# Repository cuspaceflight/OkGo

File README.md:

OkGo
====

*OkGo* is [Cambridge University Space Flight](http://cusf.co.uk)'s
rocket firing controller.

*OkGo* was designed for testing the *Quasar* hybrid rocket motor.  It allowed
remote (over 100m of wire) control of the nitrous oxide valve and firing of the
ignition e-match.  It was constructed using an ad-hoc point-to-point layout.
An entirely passive design, it simply uses mechanical switches to trigger
relays.  It was later upgraded to control two valves, one of which passed a low
flow of nitrous oxide to help start the motor.

*OkGo 2* was a full redesign for the launch of *Martlet 2*.  Due to the
increased safety radius (on the order of 500m) radio control is to be used.  It
will have 4 general purpose (valve or e-match) channels with independent
continuity checking and firing, and separate firing boxes containing current
limiting resistors.

*OkGo 3* is another full redesign for the launch of *Martlet 3*.  It will
continuity check and ignite a single channel with a constant-current drive.
Ignition and control will be small and light for portability.

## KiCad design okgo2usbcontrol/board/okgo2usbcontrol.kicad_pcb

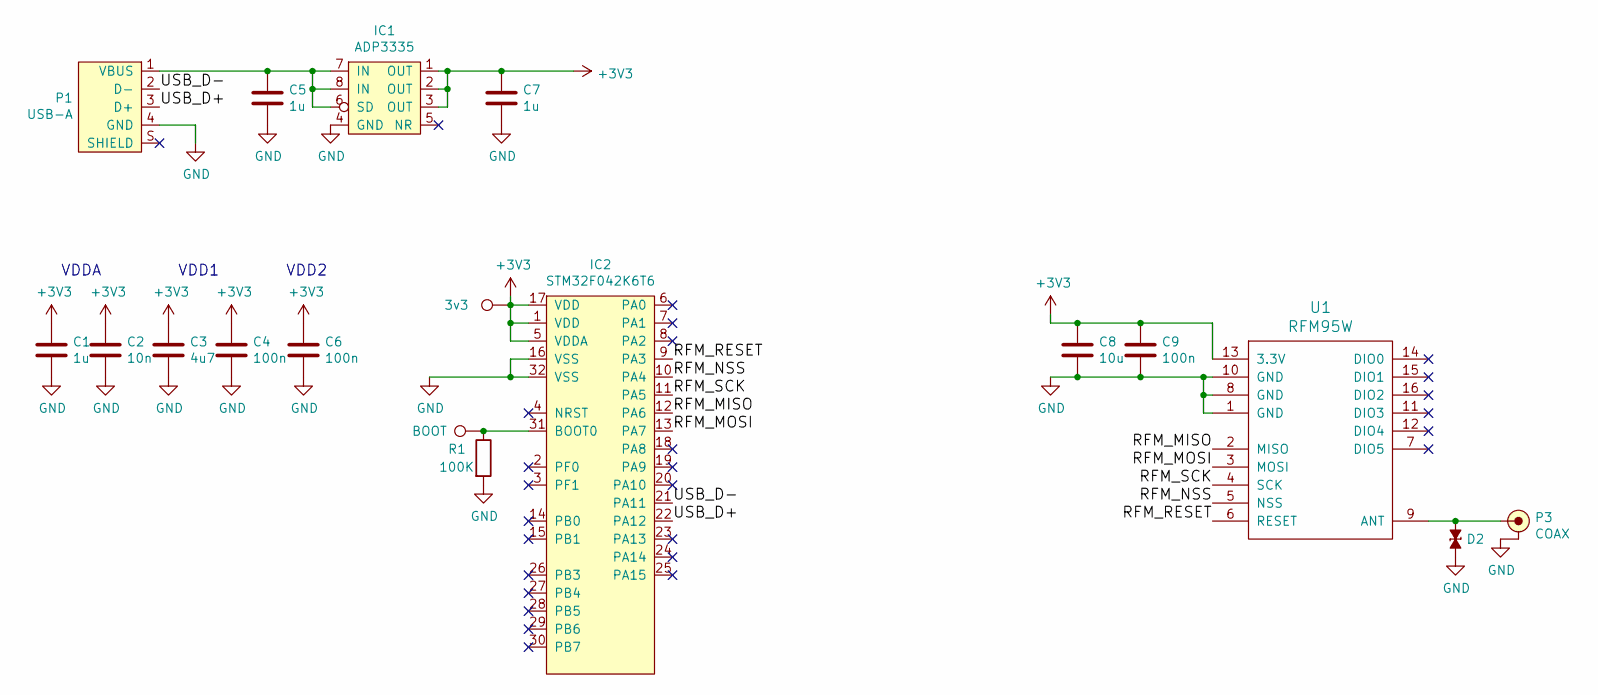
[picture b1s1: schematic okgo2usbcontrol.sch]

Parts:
C1, C5, C7: 1u; 0402
C2: 10n; 0402
C3: 4u7; 0402
C4, C6, C9: 100n; 0402
C8: 10u; 0402
D2: ESD_DIODE; 0603
IC1: ADP3335; MSOP-8; Farnell 2067775
IC2: STM32F042K6T6; LQFP-32; Farnell 2750629
P1: USB-A; USB-A_M_Edge; Farnell 2067044
P3: COAX; SMA-EDGE; Farnell 1608592
R1: 100K; 0402
U1: RFM95W
W1: BOOT; PokyPad
W2: 3v3; PokyPad

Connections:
+3V3: C1.1, C2.1, C3.1, C4.1, C6.1, C7.1, C8.1, C9.1, IC1.1 (OUT), IC1.2 (OUT), IC1.3 (OUT), IC2.1 (VDD), IC2.5 (VDDA), IC2.17 (VDD), U1.13 (3.3V), W2.1
/RFM_MISO: IC2.12 (PA6), U1.2 (MISO)
/RFM_MOSI: IC2.13 (PA7), U1.3 (MOSI)
/RFM_NSS: IC2.10 (PA4), U1.5 (NSS)
/RFM_RESET: IC2.9 (PA3), U1.6 (RESET)
/RFM_SCK: IC2.11 (PA5), U1.4 (SCK)
/USB_D+: IC2.22 (PA12), P1.3 (D+)
/USB_D-: IC2.21 (PA11), P1.2 (D-)
GND: C1.2, C2.2, C3.2, C4.2, C5.2, C6.2, C7.2, C8.2, C9.2, D2.2, IC1.4 (GND), IC2.16 (VSS), IC2.32 (VSS), P1.4 (GND), P3.2 (GND), R1.2, U1.1 (GND), U1.8 (GND), U1.10 (GND)
unnamed: C5.1, IC1.6 (SD), IC1.7 (IN), IC1.8 (IN), P1.1 (VBUS)
unnamed: D2.1, P3.1 (RF), U1.9 (ANT)
unnamed: IC2.31 (BOOT0), R1.1, W1.1

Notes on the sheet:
VDDA
VDD1
VDD2

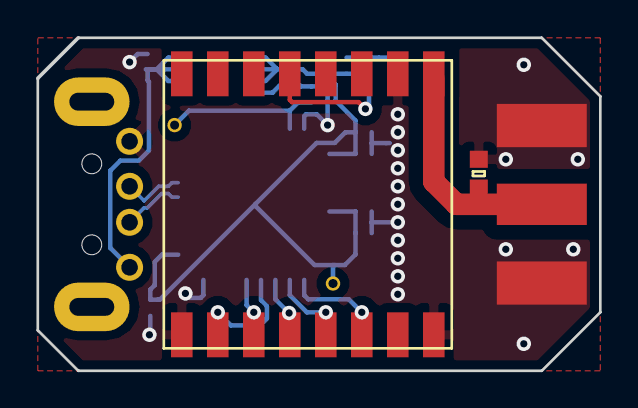
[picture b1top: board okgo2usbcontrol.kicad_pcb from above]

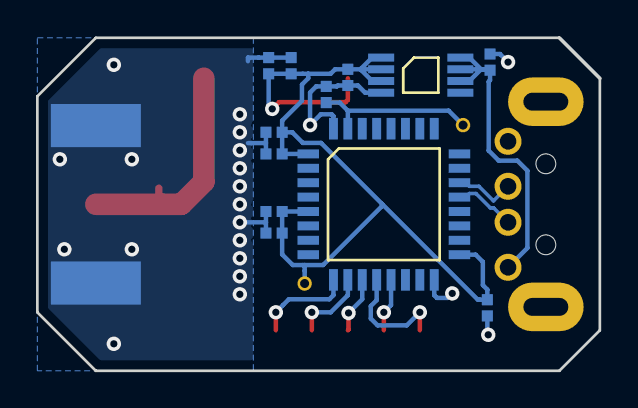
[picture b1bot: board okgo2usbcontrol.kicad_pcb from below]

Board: 2 copper layers, 31.2 x 18.5 mm, 18 parts (14 on the bottom side), 12 nets.

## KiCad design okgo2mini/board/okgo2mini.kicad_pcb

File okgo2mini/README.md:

# Design
* A mini version of OkGo 2 ignition, compatible with OkGo 2 control
* Use STM32F0 and RFM95W circuit from OkGo 2 ignition
    * If I'm careful I could make it pin-compatible and use the same firmware
      as OkGo 2, or just with minimal modification
* Use battery charge/management circuit from Toad/Linetime
    * Has only had minimal testing on Linetime. Wait for Toad to be tested
      before committing to this.
* Use 1A constant current firer from latest m3pyro
# Parts
* Nana plugs: red CN16308 black CN16305
* High retention red USB-B 1753809
* Red Hammond extruded aluminium case 2469292

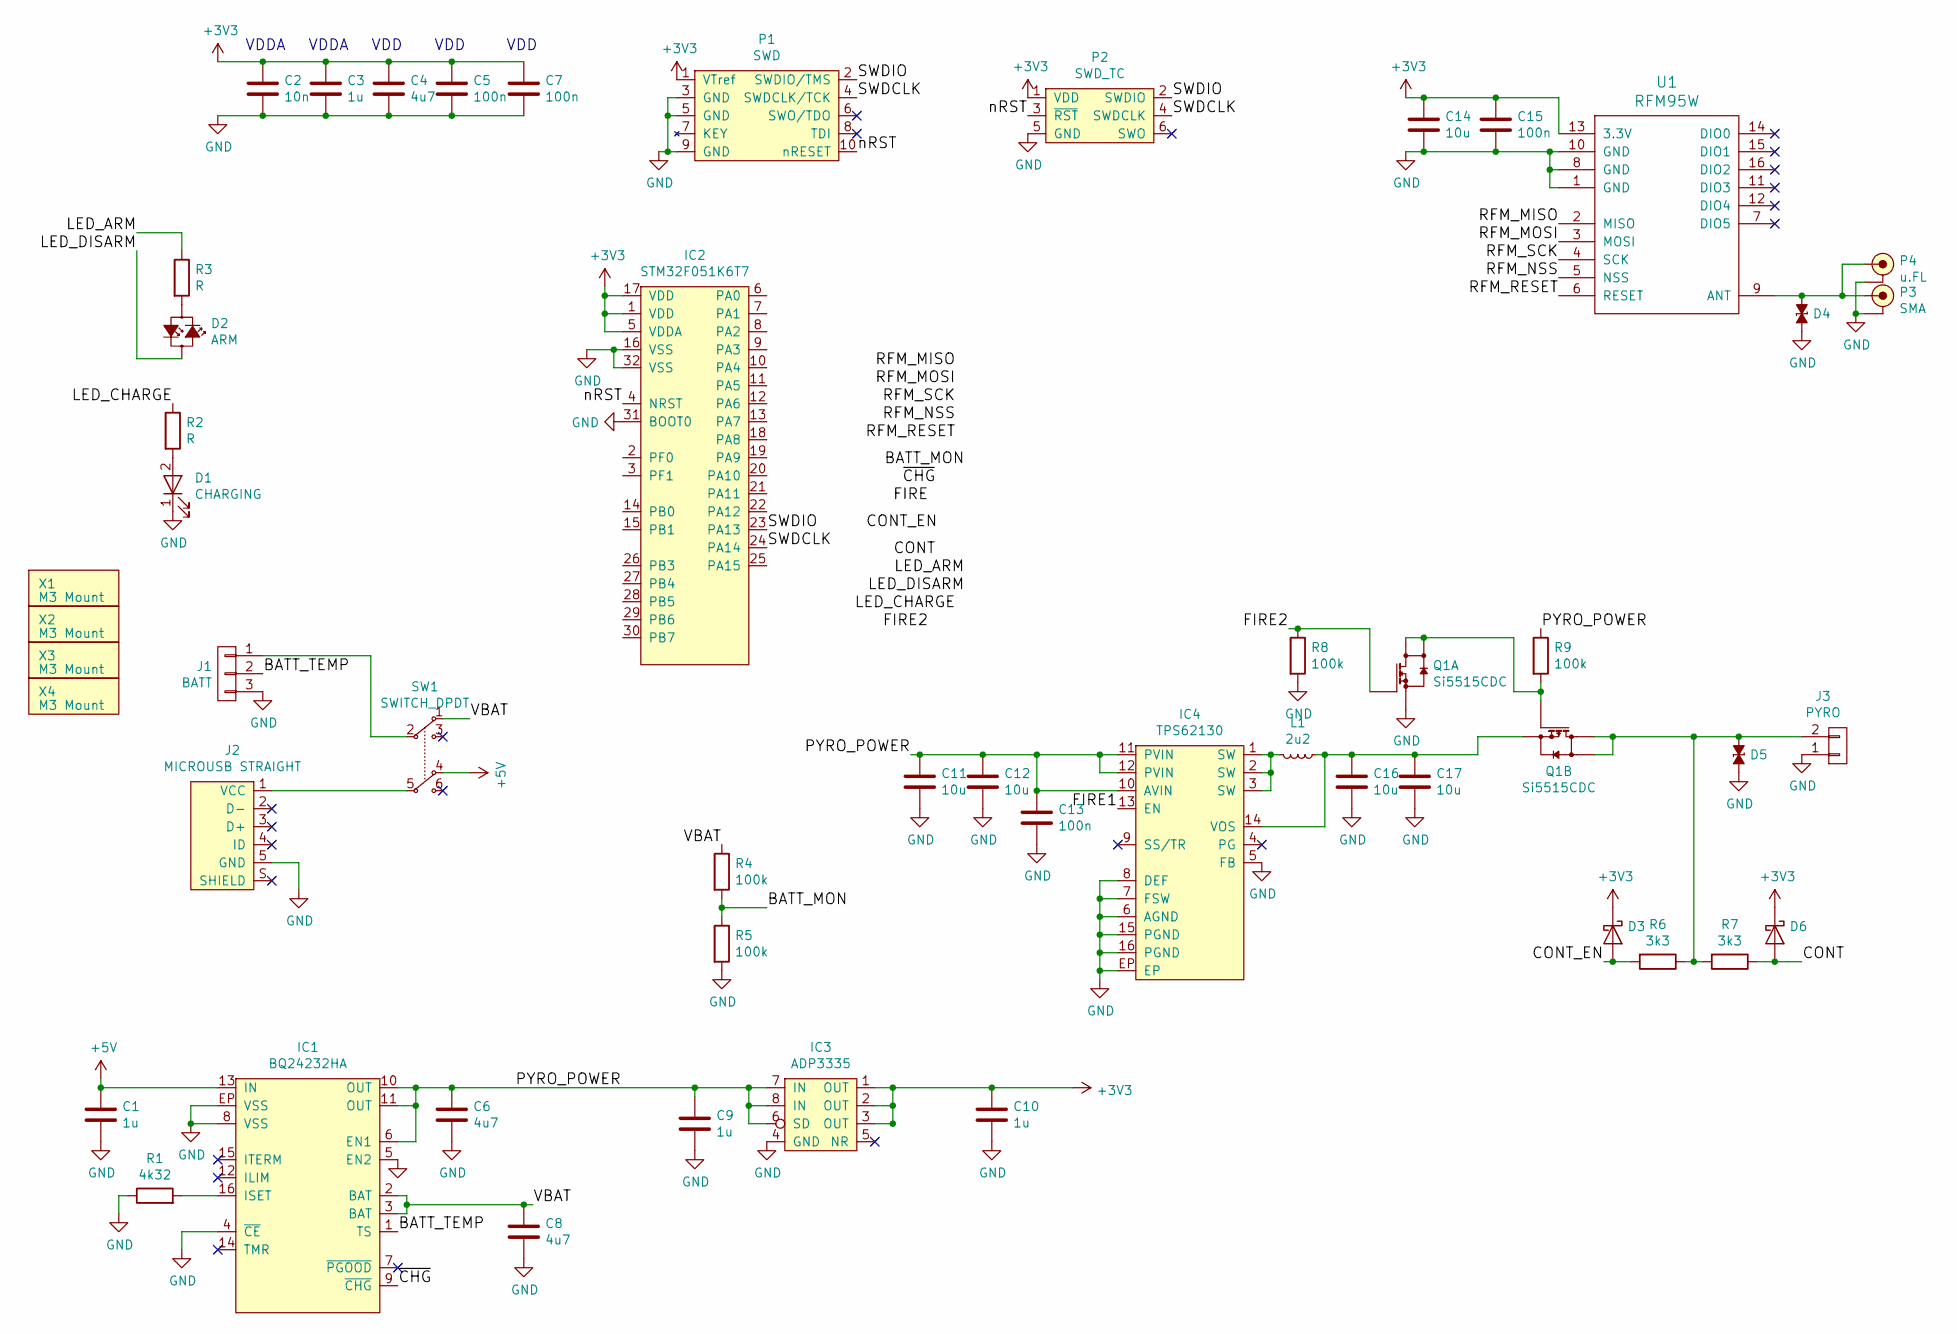
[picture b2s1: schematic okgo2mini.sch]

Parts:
C1, C3, C9, C10: 1u; 0603
C2: 10n; 0603
C4, C6, C8: 4u7; 0603
C5, C7, C13, C15: 100n; 0603
C11, C12, C14, C16, C17: 10u; 0603
D1: CHARGING; LED_D3.0mm; Farnell 2610420
D2: ARM; LED_D3.0mm; Farnell 2079908
D3, D6: PMEG2005AEA; SOD-323; Farnell 8737843
D4, D5: ESD_DIODE; 0603; Farnell 2368173
IC1: BQ24232HA; QFN-16-EP-TI; Farnell 2576286
IC2: STM32F051K6T7; LQFP-32; Farnell 2432085
IC3: ADP3335; MSOP-8; Farnell 2067775
IC4: TPS62130; QFN-16-EP-TI; Farnell 2361246
J1: BATT; S03B-PASK-2
J2: MICROUSB STRAIGHT; USB_Micro_B_Vertical; Farnell 2614949
J3: PYRO; S02B-PASK-2
L1: 2u2; XFL4020; Farnell 2289216
P1: SWD; FTSH-105-01-F-D-K
P2: SWD_TC; TC2030-NL
P3: SMA; SMA-EDGE; Farnell 1608592
P4: u.FL; uFL-R-SMT; Farnell 1688077
Q1: Si5515CDC; ChipFET-1206-8; Farnell 2335332
R1: 4k32; 0603
R2, R3: R; 0603
R4, R5, R8, R9: 100k; 0603
R6, R7: 3k3; 0603
SW1: SWITCH_DPDT; 120x-M1-xx-C; Farnell 9574743
U1: RFM95W; Farnell RF00490
X1, X2, X3, X4: M3 Mount; M3_MOUNT

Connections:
+3V3: C2.1, C3.1, C4.1, C5.1, C7.1, C10.1, C14.1, C15.1, D3.1 (K), D6.1 (K), IC2.1 (VDD), IC2.5 (VDDA), IC2.17 (VDD), IC3.1 (OUT), IC3.2 (OUT), IC3.3 (OUT), P1.1 (VTref), P2.1 (VDD), U1.13 (3.3V)
+5V: C1.1, IC1.13 (IN), SW1.4
/BATT_MON: R4.2, R5.1
/BATT_TEMP: IC1.1 (TS), J1.2
/CONT: D6.2 (A), R7.1
/CONT_EN: D3.2 (A), R6.2
/FIRE1: IC4.13 (EN)
/FIRE2: Q1.2 (G1), R8.1
/LED_ARM: R3.1
/LED_CHARGE: R2.1
/LED_DISARM: D2.2 (A)
/PYRO_POWER: C6.1, C9.1, C11.1, C12.1, C13.1, IC1.6 (EN1), IC1.10 (OUT), IC1.11 (OUT), IC3.6 (SD), IC3.7 (IN), IC3.8 (IN), IC4.10 (AVIN), IC4.11 (PVIN), IC4.12 (PVIN), R9.1
/RFM_MISO: U1.2 (MISO)
/RFM_MOSI: U1.3 (MOSI)
/RFM_NSS: U1.5 (NSS)
/RFM_RESET: U1.6 (RESET)
/RFM_SCK: U1.4 (SCK)
/SWDCLK: IC2.24 (PA14), P1.4 (SWDCLK/TCK), P2.4 (SWDCLK)
/SWDIO: IC2.23 (PA13), P1.2 (SWDIO/TMS), P2.2 (SWDIO)
/VBAT: C8.1, IC1.2 (BAT), IC1.3 (BAT), R4.1, SW1.1
/nRST: IC2.4 (NRST), P1.10 (nRESET), P2.3 (~RST)
/~CHG: IC1.9 (~CHG)
GND: C1.2, C2.2, C3.2, C4.2, C5.2, C6.2, C7.2, C8.2, C9.2, C10.2, C11.2, C12.2, C13.2, C14.2, C15.2, C16.2, C17.2, D1.1 (K), D4.2, D5.2, IC1.4 (~CE), IC1.5 (EN2), IC1.8 (VSS), IC1.EP (VSS), IC2.16 (VSS), IC2.31 (BOOT0), IC2.32 (VSS), IC3.4 (GND), IC4.5 (FB), IC4.6 (AGND), IC4.7 (FSW), IC4.8 (DEF), IC4.15 (PGND), IC4.16 (PGND), IC4.EP, J1.3, J2.5 (GND), J3.1, P1.3 (GND), P1.5 (GND), P1.9 (GND), P2.5 (GND), P3.2 (GND), P4.2 (GND), Q1.1 (S1), R1.1, R5.2, R8.2, U1.1 (GND), U1.8 (GND), U1.10 (GND)
unnamed: C16.1, C17.1, IC4.14 (VOS), L1.1, Q1.3 (S2)
unnamed: D1.2 (A), R2.2
unnamed: D2.1 (K), R3.2
unnamed: D4.1, P3.1 (RF), P4.1 (RF), U1.9 (ANT)
unnamed: D5.1, J3.2, Q1.5 (D2), Q1.6 (D2), R6.1, R7.2
unnamed: IC1.16 (ISET), R1.2
unnamed: IC4.1 (SW), IC4.2 (SW), IC4.3 (SW), L1.2
unnamed: J1.1, SW1.2
unnamed: J2.1 (VCC), SW1.5
unnamed: Q1.4 (G2), Q1.7 (D1), Q1.8 (D1), R9.2

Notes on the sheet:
VDDA
VDD

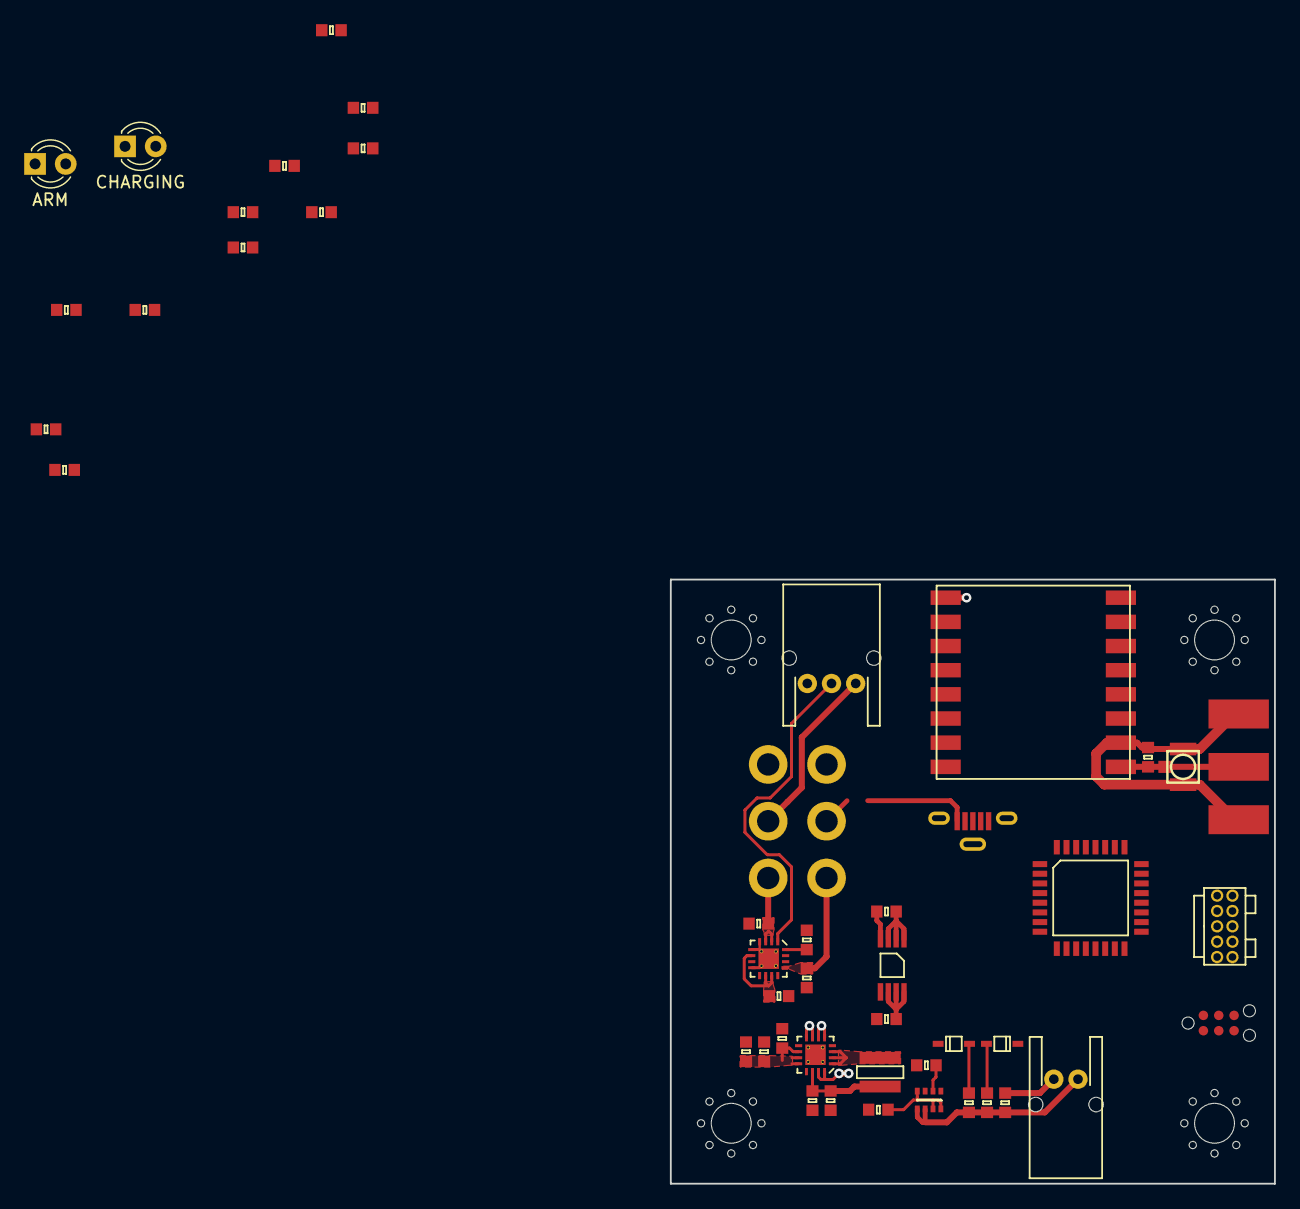
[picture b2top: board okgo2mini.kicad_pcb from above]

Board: 2 copper layers, 50.0 x 50.0 mm, 51 parts (1 on the bottom side), 23 nets.

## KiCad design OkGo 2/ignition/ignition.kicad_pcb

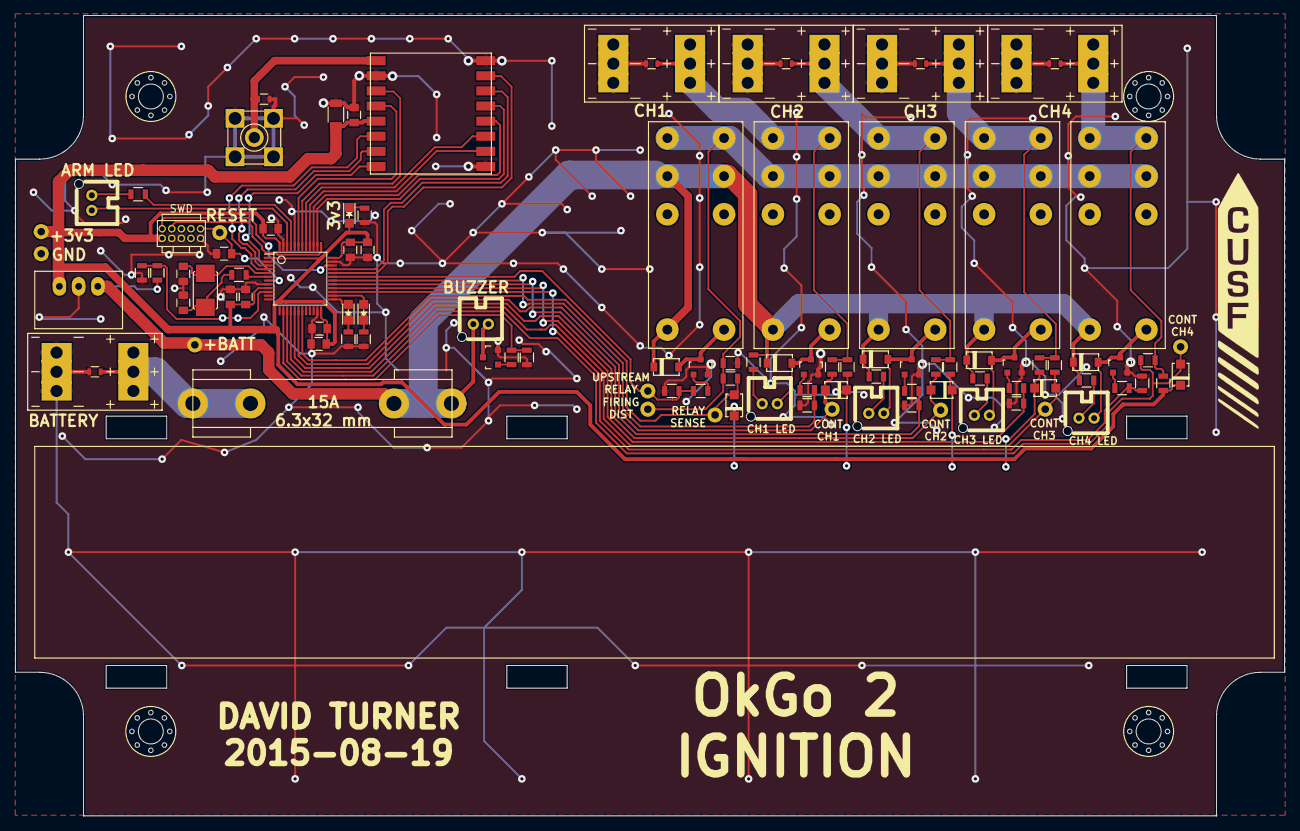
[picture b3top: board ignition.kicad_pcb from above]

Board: 2 copper layers, 167.9 x 105.9 mm, 108 parts (0 on the bottom side), 63 nets.

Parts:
C101, C102, C104, C105, C109: 100n; C_0805
C103, C106: 4u7; C_0805
C107: 10n; C_0805
C108: 100u; C_1206
C110: 1u; C_0805
C111, C112: 15p; C_0805
D101, D103, D206, D210, D214, D218: TVS_small; R_0603
D104: RED; LED-0805
D105: GREEN; LED-0805
D106: YELLOW; LED-0805
D201, D205, D209, D213, D217: MBR2H200SFT1G; SOD-123FL
D202, D204, D208, D212, D216: D; SOD-123F
F101: 6.3x32; 6x32_fuseclip
K201, K202, K203, K204, K205: 16A SPST; Relay_RT314
M3_MOUNT, M3_MOUNT#2, M3_MOUNT#3, M3_MOUNT#4: VAL**; M3_MOUNT_FANCY
P105: BATT; PCB_SPADE
P107: ARM_LED; JST-PA-2-VERT
P109: BUZZ; JST-PA-2-VERT
P111: SMA; SMA_upright
P201: CH3_LED; JST-PA-2-VERT
P203: CH3; PCB_SPADE
P204: CH1_LED; JST-PA-2-VERT
P206: CH1; PCB_SPADE
P207: CH4_LED; JST-PA-2-VERT
P209: CH4; PCB_SPADE
P210: CH2_LED; JST-PA-2-VERT
P212: CH2; PCB_SPADE
Q101, Q201, Q202, Q203, Q204, Q205: BSS138BK; SOT-23
R101, R207, R212, R217, R222: 10k; R_0805
R102: 3k3; R_0805
R103: 75R; R_0805
R104: 100R; R_0805
R105, R201, R208, R213, R218, R223: 180R; R_0805
R106, R202, R204, R210, R214, R220, R224: 100k; R_0805
R107, R108, R109: R; R_0805
R203, R206, R211, R216, R221: 1k; R_0805
R205, R215: 430; R_0805
R209: 510R; R_0805
R219: 510; R_0805
TP101: BATT; TESTPOINT
TP102: GND; TESTPOINT
TP103: nRST; TESTPOINT
TP104: 3v3; TESTPOINT
TP201: FiringDist; TESTPOINT
TP202: USRelay; TESTPOINT
TP203: RelaySense; TESTPOINT
TP204: ContCH3; TESTPOINT
TP205: ContCH1; TESTPOINT
TP206: ContCH4; TESTPOINT
TP207: ContCH2; TESTPOINT
U103: SWD; FTSH-105-01-F-D-K
U105: RFM95W
U106: STM32F071CBT6; LQFP48_ST
U107: TSR 0.5-2433; TSR-0_5
Y101: 8MHz; XTAL50x32

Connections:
+3V3: C101.1, C102.1, C103.1, C105.1, C106.1, C107.1, C108.1, C109.1, C110.1, D104.2, D202.1, D204.1, D208.1, D212.1, D216.1, R206.1, R211.1, R216.1, R221.1, TP104.1, U103.1, U105.13, U106.1, U106.9, U106.24, U106.36, U106.48, U107.3
+BATT: D201.1, D205.1, D209.1, D213.1, D217.1, F101.2, K201.2, K201.3, K202.2, K203.2, K204.2, K205.2, P109.2, R101.1, R205.2, R209.2, R215.2, R219.2, TP101.1, U107.1
/ARM_LED: R103.2, U106.45
/BATT_MON: R101.2, R102.1, U106.10
/BUZZER: R105.2, R106.1, U106.14
/DISARM_LED: P107.1, U106.46
/RFM_DIO0: U105.14, U106.4
/RFM_DIO1: U105.15, U106.3
/RFM_DIO2: U105.16, U106.2
/RFM_DIO3: U105.11, U106.42
/RFM_DIO4: U105.12, U106.43
/RFM_DIO5: U105.7, U106.32
/RFM_MISO: U105.2, U106.40
/RFM_MOSI: U105.3, U106.41
/RFM_NSS: U105.5, U106.38
/RFM_RESET: U105.6, U106.33
/RFM_SCK: U105.4, U106.39
/SWDCLK: U103.4, U106.37
/SWDIO: U103.2, U106.34
/firing/CONT_CH1: D208.2, R212.1, TP205.1, U106.18
/firing/CONT_CH2: D216.2, R222.1, TP207.1, U106.17
/firing/CONT_CH3: D204.2, R207.1, TP204.1, U106.16
/firing/CONT_CH4: D212.2, R217.1, TP206.1, U106.15
/firing/FIRE_CH1: R213.2, R214.1, U106.30
/firing/FIRE_CH2: R223.2, R224.1, U106.29
/firing/FIRE_CH3: R208.2, R210.1, U106.28
/firing/FIRE_CH4: R218.2, R220.1, U106.27
/firing/FIRING_DIST: K201.4, K202.3, K203.3, K204.3, K205.3, R203.2, R204.1, TP201.1
/firing/RELAY_SENSE: D202.2, R203.1, TP203.1, U106.19
/firing/UPSTREAM_RELAY: R201.2, R202.2, TP202.1, U106.31
/nRST: C104.1, TP103.1, U103.10, U106.7
GND: C101.2, C102.2, C103.2, C104.2, C105.2, C106.2, C107.2, C108.2, C109.2, C110.2, C111.2, C112.2, D101.2, D103.2, D206.2, D210.2, D214.2, D218.2, P105.1, P111.2, P111.3, P111.4, P111.5, P203.1, P206.1, P209.1, P212.1, Q101.2, Q201.2, Q202.2, Q203.2, Q204.2, Q205.2, R102.2, R106.2, R107.2, R108.2, R109.2, R202.1, R204.2, R210.2, R214.2, R220.2, R224.2, TP102.1, U103.3, U103.5, U103.9, U105.1, U105.8, U105.10, U106.8, U106.23, U106.35, U106.44, U106.47, U107.2
unnamed: C111.1, R104.1, Y101.2
unnamed: C112.1, U106.5, Y101.1
unnamed: D101.1, F101.1, P105.2
unnamed: D103.1, P111.1, U105.9
unnamed: D104.1, R107.1
unnamed: D105.1, R108.1
unnamed: D105.2, U106.25
unnamed: D106.1, R109.1
unnamed: D106.2, U106.26
unnamed: D201.2, K201.1, Q201.3
unnamed: D205.2, K202.1, P201.1, Q202.3
unnamed: D206.1, K202.4, P203.2, R206.2, R207.2
unnamed: D209.2, K203.1, P204.1, Q203.3
unnamed: D210.1, K203.4, P206.2, R211.2, R212.2
unnamed: D213.2, K204.1, P207.1, Q204.3
unnamed: D214.1, K204.4, P209.2, R216.2, R217.2
unnamed: D217.2, K205.1, P210.1, Q205.3
unnamed: D218.1, K205.4, P212.2, R221.2, R222.2
unnamed: P107.2, R103.1
unnamed: P109.1, Q101.3
unnamed: P201.2, R205.1
unnamed: P204.2, R209.1
unnamed: P207.2, R215.1
unnamed: P210.2, R219.1
unnamed: Q101.1, R105.1
unnamed: Q201.1, R201.1
unnamed: Q202.1, R208.1
unnamed: Q203.1, R213.1
unnamed: Q204.1, R218.1
unnamed: Q205.1, R223.1
unnamed: R104.2, U106.6

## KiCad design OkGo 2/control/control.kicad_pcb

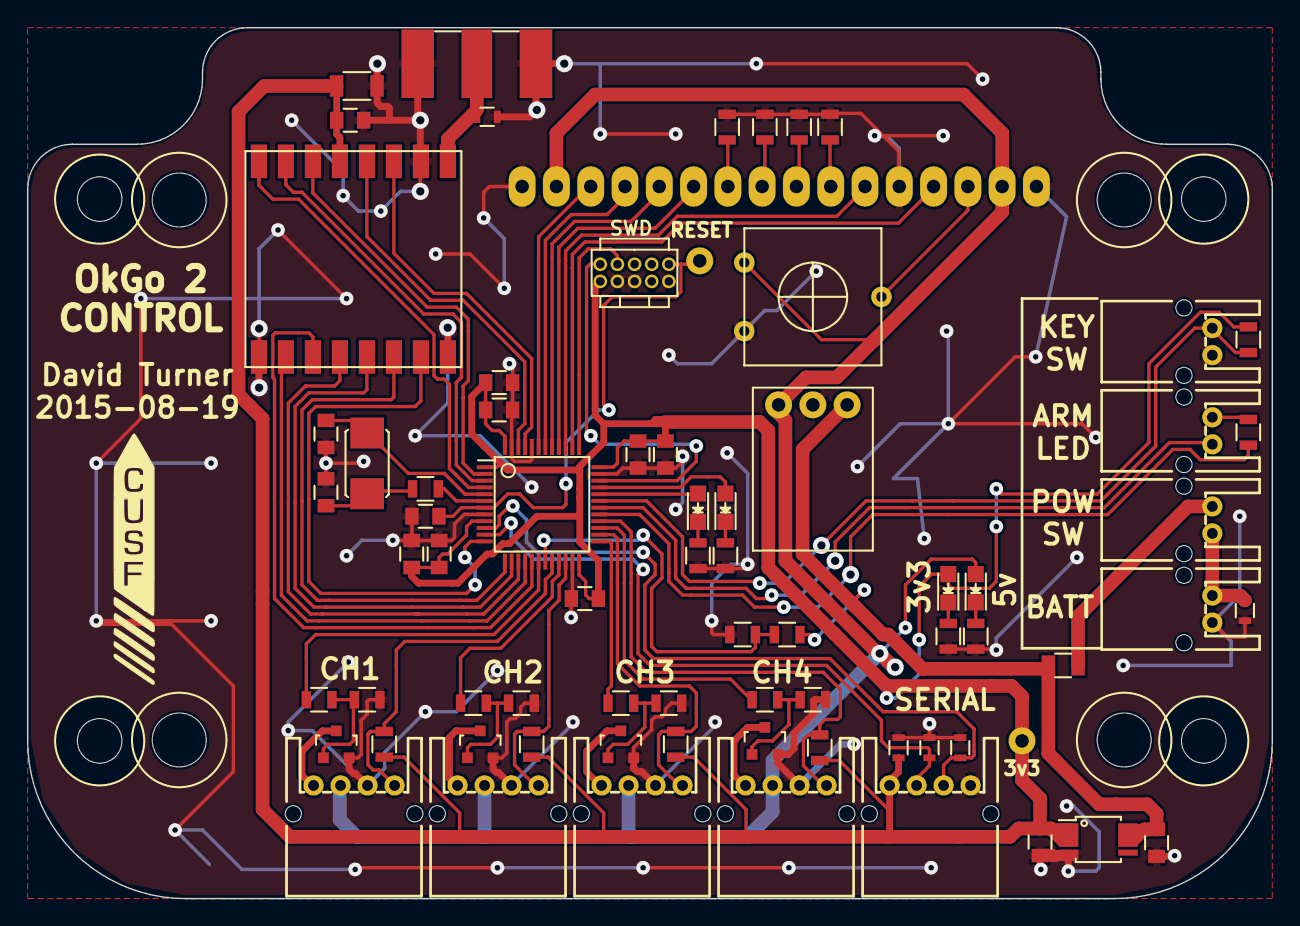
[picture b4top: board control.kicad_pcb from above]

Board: 2 copper layers, 92.2 x 64.5 mm, 77 parts (1 on the bottom side), 64 nets.

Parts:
C101, C102, C104, C108, C112: 100n; C_0805
C103, C105: 4u7; C_0805
C106: 10n; C_0805
C107: 1u; C_0805
C109, C110: 15p; C_0805
C111: 100u; C_1206
C113, C114: 2u2; C_0805
D101, D103, D104, D105, D106: TVS_small; R_0603
D107, D110: RED; LED-0805
D108: GREEN; LED-0805
D109: YELLOW; LED-0805
F101: PTC; polyfuse0805
M3_MOUNT, M3_MOUNT#2, M3_MOUNT#3, M3_MOUNT#4: VAL**; M3_MOUNT
P102: KEYSW; JST-PA-2
P105: BATT; JST-PA-2
P106: ARM_LED; JST-PA-2
P108: SMA; SMA-142-0701-801
P110: POWER_SW; JST-PA-2
P111: SERIAL; JST-PA-4
P201: CH1; JST-PA-4
P202: CH2; JST-PA-4
P205: CH3; JST-PA-4
P206: CH4; JST-PA-4
Q201, Q202, Q203, Q204: BSS138BK; SOT-23
R101, R106, R107, R108, R109, R110, R205, R206, R211, R212: 10k; R_0805
R102: 100R; R_0805
R103: 75R; R_0805
R104: R_Small; R_0805
R105: 3k3; R_0805
R111, R112, R113: R; R_0805
R201, R202, R207, R208: 180R; R_0805
R203, R204, R209, R210: 100k; R_0805
RV101: 20k LIN; bourns3386G
TP101: nRST; TESTPOINT
TP102: 3v3; TESTPOINT
U101: SWD; FTSH-105-01-F-D-K
U102: STM32F071CBT6; LQFP48_ST
U103: pololu_S7V7F5; polulo_S7V7F5
U105: RFM95W
U106: LCD_HD44780; LCD_MC42004A6W_bare
U107: ADP3335; MSOP-8_3x3mm_Pitch0.65mm
Y101: 8MHz; XTAL50x32

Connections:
+3V3: C101.1, C102.1, C103.1, C104.1, C105.1, C106.1, C107.1, C111.2, C112.2, C114.1, D106.1, D107.2, P111.4, R101.1, R205.1, R206.1, R211.1, R212.1, TP102.1, U101.1, U102.1, U102.9, U102.24, U102.36, U102.48, U105.13, U107.1, U107.2, U107.3
+5V: D110.2, P201.3, P202.3, P205.3, P206.3, RV101.1, U103.3, U106.2, U106.15
+BATT: C113.1, F101.2, R105.1, U103.1, U107.6, U107.7, U107.8
/ARM_LED: R103.2, U102.29
/ARM_SW: P102.2, R101.2, U102.31
/BATT_MON: R105.2, R106.1, U102.19
/DISARM_LED: P106.1, U102.30
/LCD_DB4: U102.40, U106.11
/LCD_DB5: U102.41, U106.12
/LCD_DB6: U102.42, U106.13
/LCD_DB7: U102.43, U106.14
/LCD_E: U102.39, U106.6
/LCD_RS: U102.38, U106.4
/RFM_DIO0: U102.2, U105.14
/RFM_DIO1: U102.3, U105.15
/RFM_DIO2: U102.4, U105.16
/RFM_DIO3: U102.45, U105.11
/RFM_DIO4: U102.46, U105.12
/RFM_DIO5: U102.12, U105.7
/RFM_MISO: U102.16, U105.2
/RFM_MOSI: U102.17, U105.3
/RFM_NSS: U102.14, U105.5
/RFM_RESET: U102.13, U105.6
/RFM_SCK: U102.15, U105.4
/SWDCLK: U101.4, U102.37
/SWDIO: U101.2, U102.34
/controls/CH1_LED: R201.2, U102.18
/controls/CH1_SW: P201.1, R205.2, U102.20
/controls/CH2_LED: R202.2, U102.21
/controls/CH2_SW: P202.1, R206.2, U102.22
/controls/CH3_LED: R207.2, U102.25
/controls/CH3_SW: P205.1, R211.2, U102.26
/controls/CH4_LED: R208.2, U102.27
/controls/CH4_SW: P206.1, R212.2, U102.28
/nRST: C108.1, TP101.1, U101.10, U102.7
GND: C101.2, C102.2, C103.2, C104.2, C105.2, C106.2, C107.2, C108.2, C109.2, C110.2, C111.1, C112.1, C113.2, C114.2, D101.2, D103.1, D104.2, D105.2, D106.2, P102.1, P105.1, P108.2, P108.3, P108.4, P108.5, P111.1, P201.2, P202.2, P205.2, P206.2, Q201.2, Q202.2, Q203.2, Q204.2, R104.2, R106.2, R107.2, R108.2, R109.2, R110.2, R111.2, R112.2, R113.2, R203.2, R204.2, R209.2, R210.2, RV101.3, U101.3, U101.5, U101.9, U102.8, U102.23, U102.35, U102.44, U102.47, U103.2, U105.1, U105.8, U105.10, U106.1, U106.5, U106.16, U107.4
unnamed: C109.1, R102.2, Y101.2
unnamed: C110.1, U102.5, Y101.1
unnamed: D101.1, P105.2, P110.1
unnamed: D103.2, P108.1, U105.9
unnamed: D104.1, P111.2, U102.10
unnamed: D105.1, P111.3, U102.11
unnamed: D107.1, R104.1
unnamed: D108.1, R111.1
unnamed: D108.2, U102.33
unnamed: D109.1, R112.1
unnamed: D109.2, U102.32
unnamed: D110.1, R113.1
unnamed: F101.1, P110.2
unnamed: P106.2, R103.1
unnamed: P201.4, Q201.3
unnamed: P202.4, Q202.3
unnamed: P205.4, Q203.3
unnamed: P206.4, Q204.3
unnamed: Q201.1, R201.1, R203.1
unnamed: Q202.1, R202.1, R204.1
unnamed: Q203.1, R207.1, R209.1
unnamed: Q204.1, R208.1, R210.1
unnamed: R102.1, U102.6
unnamed: R107.1, U106.10
unnamed: R108.1, U106.9
unnamed: R109.1, U106.8
unnamed: R110.1, U106.7
unnamed: RV101.2, U106.3

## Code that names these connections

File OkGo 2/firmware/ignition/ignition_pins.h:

#ifndef CONTROL_PINS_H
#define CONTROL_PINS_H

/* Clock GPIOs, set pin modes (except radio) */
void ignition_pins_init(void);

/* Set buzzer DAC output value. */
void ignition_buzzer_set(uint8_t value);

/* LEDs */
#define LED_GREEN           GPIO13
#define LED_GREEN_PORT      GPIOB
#define LED_YELLOW          GPIO12
#define LED_YELLOW_PORT     GPIOB

#define LED_ARM             GPIO8
#define LED_ARM_PORT        GPIOB
#define LED_DISARM          GPIO9
#define LED_DISARM_PORT     GPIOB

/* Piezo buzzer */
#define BUZZER              GPIO4
#define BUZZER_PORT         GPIOA

/* Upstream relay and firing channels */
#define UPSTREAM_RELAY      GPIO10
#define UPSTREAM_RELAY_PORT GPIOA
#define FIRE_CH1            GPIO9
#define FIRE_CH1_PORT       GPIOA
#define FIRE_CH2            GPIO8
#define FIRE_CH2_PORT       GPIOA
#define FIRE_CH3            GPIO15
#define FIRE_CH3_PORT       GPIOB
#define FIRE_CH4            GPIO14
#define FIRE_CH4_PORT       GPIOB

/* Radio */
#define RFM_NSS             GPIO15
#define RFM_NSS_PORT        GPIOA
#define RFM_RESET           GPIO12
#define RFM_RESET_PORT      GPIOA
#define RFM_DIO0            GPIO15
#define RFM_DIO0_PORT       GPIOC
#define RFM_DIO1            GPIO14
#define RFM_DIO1_PORT       GPIOC
#define RFM_DIO2            GPIO13
#define RFM_DIO2_PORT       GPIOC
#define RFM_DIO3            GPIO6
#define RFM_DIO3_PORT       GPIOB
#define RFM_DIO4            GPIO7
#define RFM_DIO4_PORT       GPIOB
#define RFM_DIO5            GPIO11
#define RFM_DIO5_PORT       GPIOA
#define RFM_NSS             GPIO15
#define RFM_NSS_PORT        GPIOA
#define RFM_SCK             GPIO3
#define RFM_SCK_PORT        GPIOB
#define RFM_MISO            GPIO4
#define RFM_MISO_PORT       GPIOB
#define RFM_MOSI            GPIO5
#define RFM_MOSI_PORT       GPIOB

/* Analog pins */
#define BATT_MON            GPIO0
#define BATT_MON_PORT       GPIOA
#define RELAY_SENSE         GPIO1
#define RELAY_SENSE_PORT    GPIOB
#define CONT_CH1            GPIO0
#define CONT_CH1_PORT       GPIOB
#define CONT_CH2            GPIO7
#define CONT_CH2_PORT       GPIOA
#define CONT_CH3            GPIO6
#define CONT_CH3_PORT       GPIOA
#define CONT_CH4            GPIO5
#define CONT_CH4_PORT       GPIOA

#endif

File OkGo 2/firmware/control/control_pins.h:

#ifndef CONTROL_PINS_H
#define CONTROL_PINS_H

#include <libopencm3/stm32/gpio.h>

/* Clock GPIOs, set pin modes (except radio and display) */
void control_pins_init(void);

/* LEDs */
#define LED_GREEN       GPIO12
#define LED_GREEN_PORT  GPIOA
#define LED_YELLOW      GPIO11
#define LED_YELLOW_PORT GPIOA

#define LED_ARM         GPIO8
#define LED_ARM_PORT    GPIOA
#define LED_DISARM      GPIO9
#define LED_DISARM_PORT GPIOA

/* Keyswitch */
#define SW_KEY          GPIO10
#define SW_KEY_PORT     GPIOA

/* Channels - switches and LEDs */
#define LED_CH1         GPIO0
#define LED_CH1_PORT    GPIOB
#define LED_CH2         GPIO10
#define LED_CH2_PORT    GPIOB
#define LED_CH3         GPIO12
#define LED_CH3_PORT    GPIOB
#define LED_CH4         GPIO14
#define LED_CH4_PORT    GPIOB

#define SW_CH1          GPIO2
#define SW_CH1_PORT     GPIOB
#define SW_CH2          GPIO11
#define SW_CH2_PORT     GPIOB
#define SW_CH3          GPIO13
#define SW_CH3_PORT     GPIOB
#define SW_CH4          GPIO15
#define SW_CH4_PORT     GPIOB

/* LCD */
#define LCD_RS          GPIO15
#define LCD_RS_PORT     GPIOA
#define LCD_E           GPIO3
#define LCD_E_PORT      GPIOB
#define LCD_DB4         GPIO4
#define LCD_DB4_PORT    GPIOB
#define LCD_DB5         GPIO5
#define LCD_DB5_PORT    GPIOB
#define LCD_DB6         GPIO6
#define LCD_DB6_PORT    GPIOB
#define LCD_DB7         GPIO7
#define LCD_DB7_PORT    GPIOB

/* Radio */
#define RFM_NSS         GPIO4
#define RFM_NSS_PORT    GPIOA
#define RFM_SCK         GPIO5
#define RFM_SCK_PORT    GPIOA
#define RFM_MISO        GPIO6
#define RFM_MISO_PORT   GPIOA
#define RFM_MOSI        GPIO7
#define RFM_MOSI_PORT   GPIOA
#define RFM_RESET       GPIO3
#define RFM_RESET_PORT  GPIOA
#define RFM_DIO0        GPIO13
#define RFM_DIO0_PORT   GPIOC
#define RFM_DIO1        GPIO14
#define RFM_DIO1_PORT   GPIOC
#define RFM_DIO2        GPIO15
#define RFM_DIO2_PORT   GPIOC
#define RFM_DIO3        GPIO8
#define RFM_DIO3_PORT   GPIOB
#define RFM_DIO4        GPIO9
#define RFM_DIO4_PORT   GPIOB
#define RFM_DIO5        GPIO2
#define RFM_DIO5_PORT   GPIOA

/* Analog pins */
#define BATT_MON        GPIO1
#define BATT_MON_PORT   GPIOB

#endif

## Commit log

2012-11-25 Initial schematic commit
2012-11-25 Finished first rev of schematic
2012-11-25 Added connectors on firing/oxid loads
2012-11-25 Added test and armed LEDs
2012-11-25 Added firing box armed LED
2012-11-25 Added handy schematic labels
2012-11-25 Added a few farnell parts
2012-11-26 Updated schematic to reflect ordered parts
2012-11-26 Made schematic a little prettier
2014-02-14 Various useful paper docs
2014-03-12 Added low oxid channel to schematic
2014-03-12 Annotated schematic
2014-03-13 New wiring layout on relay coils
2015-05-10 Introducing OkGo 2 vague ideas outline.
2015-05-10 de-indented a bunch of bullets
2015-05-24 Control schematic except final pin assignment
2015-05-24 Start on ignition except firing/continuity things.
2015-05-25 Sketched character display layouts
2015-05-25 Removed RFM GPIOs, added control LCD, removed LEDs
2015-07-06 Metering display layout idea
2015-07-06 Updated schematics to new KiCAD
2015-07-07 Removed SPI pins from STM32 pinout.
    Made them generic pins for more flexibility and less weirdness. Resolves #1.
2015-07-08 Specced some parts on ignition schematic
2015-07-08 Added ESD suppression, resolves #13
    Also removed redundant pulldowns on firing channels.
2015-07-08 Upstream relay, hierarchical sheets, local labels
    * Added upstream failsafe relay and stuck relay sensing
    * Moved out firing circuits to a separate sub-sheet below control
    * Converted all global labels to local labels
    * Fixed typo in naming of nRST on control sheet
    Resolves #12.
2015-07-08 Connected nRST on ignition, fixes #10
2015-07-08 Removed pin labels from TVS
2015-07-08 Test points. Resolves #14
2015-07-08 Moved xtal drive resistors. Fixes #15
2015-07-08 Specced/valued/footprinted a lot of parts
2015-07-16 Lots and lots of part selections and small mods
2015-07-16 New power buttons and arm/disarm LED
2015-07-16 Changed and moved firing LEDs
2015-07-18 Lots of footprinting.
2015-07-18 Finished footprinting control, #7
2015-07-18 Footprinting on ignition + TPs
2015-07-18 Flyback diodes, fixes #18
2015-07-18 Lots more footprinting, mostly done.
2015-07-18 Non-handsoldering footprints, fixes #17
2015-07-20 First layout of control
2015-07-28 experimental routing of some of control
2015-07-28 4-bit LCD, pulldowns, 2-pin bicolour ARM LED
2015-07-28 Finished demo-route of control
2015-07-28 Fixed SOD123 footprint
2015-07-29 Added serial interface, resolves #19
2015-08-01 Revised control board outline
2015-08-02 2nd route of control, sans cleaning and checking
2015-08-07 Footprinting, rockers
2015-08-11 minor schematic changes
2015-08-11 ignition part arranging, chose case
2015-08-11 ignition; first attempt at placement
2015-08-12 ignition test routing somewhat done
2015-08-13 Provisional first place+pinassign+route of ignition
2015-08-13 Second route of ignition
2015-08-14 Fixed #28, fixed #24, general tidying
2015-08-14 Fixed #28 on control
2015-08-14 Tidied control 3v3,5 fixes #38
2015-08-15 Fixes #22
2015-08-17 LiPo cable tie holes, resolves #26
2015-08-17 Moved control SWD, resolves #29
2015-08-17 Changed SMA-F part
2015-08-18 Corrected a bunch of footprints, see #9
2015-08-18 More footprints, partial #9
2015-08-18 Penultimate footprinting, partial #9
2015-08-18 Finished footprinting, resolves #9
2015-08-18 Improved layout of control reg, fixes #41
2015-08-19 Chunkied vias, rerouted some bits, resolves #36
2015-08-19 Tidied control except cusf logo, partial #30
2015-08-19 Control is photo-ready. Resolves #30
2015-08-19 Silly ERC oddities
2015-08-19 Fixed weird wayward ground stitching
2015-08-19 Updated control placement to make adam happy
2015-08-19 Added LEDs to control
2015-08-19 Added LEDs to ignition
2015-08-19 Ignition copper tidying
2015-08-19 Add 3v3 TP label on control, fix silk width
2015-08-19 Ctrl: New 5V reg, more ground stitching
2015-08-19 Ctrl: Little capacitor wiggle
2015-08-20 Ignition: Tidying, GND stitching, finishing
2015-08-20 Fixed stitching derp. resolves #31
2015-08-20 Fixed derped drill file
2015-08-20 Moved vias from under fuse f/p
2015-08-20 Unmask bottom tracks on ignition
2015-08-20 fix silk label cont ch4->cont ch3
2015-08-20 add zip of gerbers to manufacture
2015-08-20 LED parts
2015-08-21 Basic firmware build env
2015-08-21 Musings on firmware and radio structure/protocols
2015-08-21 BOM updates
2015-08-25 CAM milling test
2015-08-25 gdb notes
2015-08-25 Better C091D panel mill holes
2015-08-27 Swapped ignition debug LED colours, fixes #46
2015-08-29 CAM and paste-stencil files
2015-08-29 Control LED flash test (plus other ramblings)
2015-08-29 Control's display working!
2015-08-29 control arming keyswitch demo
2015-08-29 Updated notes/docs/plans textfiles
2015-08-30 Added control channel switches+LEDs
2015-08-30 Ignition: demo relays,LEDs,piezo
2015-09-03 RFM95/SPI code begun - won't compile yet.
2015-09-08 rfm95w.c register map
2015-09-08 Firing lead part numbers
2015-09-08 Documented weird nano.specs error
2015-09-08 RFM95W registers, tx/rx functions, mode selection
2015-09-09 Xtal osc, recalibrated delay_ms, added delay_us
    Most of #50, now need to make LCD use correct delays.
2015-09-09 Radio setup and SPI init code stuff, doesn't work
2015-09-10 Made control radio SPI work
2015-09-11 Added correct ISM frequencies and restrictions
2015-09-11 Integrated radio into ignition and cleanup
2015-09-12 Tx/Rx demo working!!
2015-09-12 Added arm to tx/rx demo
2015-09-12 Added CRCs and other radio improvements
2015-09-12 Control state struct, basic display update routine
2015-09-13 Made LCD delays more sensible. Resolves #50
2015-09-13 Written (untested) ADC code
2015-09-13 Output pin default values, resolves #54
2015-09-14 Changed ADC to mv from V/10 to fix rounding bug
2015-09-14 Wrote all of the packetisation stuff. CRC problems.
2015-09-14 Fixed silly CRC err because tx packet len broke
2015-09-15 Added async receive radio code, more crc problems
2015-09-15 Added flash/debug to makefiles
2015-09-15 Channel continuity code
2015-09-16 Silly makefile derp
2015-09-16 Switched to boost PA to fix low tx power issue
2015-09-16 Default both sides to 10dBm tx power
2015-09-16 Added magic values for open and hi ch resistance
2015-09-16 Bumped armed transmit-rate, reduced chip rate
2015-09-16 Fixed ADC issues, resolves #53
    Settling time was too low, reading to erroneous ADC readings.
    Clamp diode on continuity has 5uA leakage which, through the 10k limit
    resistor, gives a (somewhat variable) 50mV offset at low resistances, leading
    to 0ohms looking like 45-50ohms. Bodged this by subtracting the 50mV offset.
2015-09-17 Wrote basic ignition buzzer DAC code (untested)
    Toward #55
2015-09-18 Added control window CAM files
2015-09-18 Clock DAC periph, found good buzzer DAC values.
2015-09-18 systick skeletons
2015-09-19 Fixed bug in control battery voltage rounding
2015-09-19 Added systick timer/delays, resolves #56
2015-09-19 Added splash screens (normal/arm/wdt) resolves #64
2015-09-19 Reduced packet rate for reliability
2015-09-19 Continuity error detection
2015-09-19 Flight mode.
2015-09-20 Initial commit on md5-hmac-test
2015-09-20 MD5 proof of concept application
2015-09-20 Working linkable MD5 library
2015-09-20 Working HMAC-MD5 demo
2015-09-20 Imported HMAC+MD5 libs, stitched hmac into tx+rx
    Currently bad static key.
2015-09-20 new control display layout
2015-09-21 Actually retrieve packet RSSIs
2015-09-22 RSSI value scaling. Resolves #60
2015-09-22 Added compiletime switchable RSSI/SNR display
2015-09-22 Added actual key, fixed some consts
2015-09-23 Ignition async mainloop, resolves #67
2015-09-25 Packet loss/drop handling, resolves #69
2015-09-25 Don't blip continuities on bad packets
2015-09-25 Control display ignition channel firing status
    Resolves #68
2015-09-25 Beeping (hardcoded volume)
2015-09-25 Swapped both radios to 915MHz for USA usage
2015-09-25 Buzzer volume settings
    Resolves #58
2015-09-25 Bumped chipping, reduced armed packet rate
2015-09-29 Swapped both radios back to 868 for UK
2015-10-11 test commit
2016-01-25 Added key stuff to readme
2016-01-25 Fixed key path
2016-02-23 fixed mrkdown codeblock newlines
2017-01-29 Fixed lifetime bug in hmac.c
    Instead of copying the new hashed key into the key variable (which is
    const) I reassign the key pointer to the new buffer containing the
    hashed key. But this buffer has a short lifetime which doesn't last for
    the rest of the function. For this fix I move the new buffer declaration
    so its lifetime lasts long enough.
2017-01-29 Fixed whitespace style issues in C source/headers
    Mostly hard tabs instead of 4x spaces, and occasionally whitespace at
    the end of lines.
2017-01-29 Actually clean common directory.
2017-01-29 Remove prototype for unused display_update function
2017-02-22 OkGo 3!
2017-02-28 remove space from okgo3 filename
2017-02-28 update readme, rename to okgo3
2017-02-28 added various parts inc display
2017-03-01 Bump agg-kicad for nightly kicad fix
2017-08-10 okgo2mini
2017-08-18 Most of okgo2mini schematic
2017-08-18 okgo2 usb controller
2017-08-18 Added USB_Micro_B Vertical Connector footprint
2017-08-18 switches for okgo2 mini and usb
2017-08-18 Add USB A board edge connector
2017-08-18 New art for upright USB micro
2017-08-18 Added footprint for 7101MD9V3BE switch
2017-08-18 Added JSX08001SAQNL slide switch footprint
2017-08-18 Make mechanical retention pads not have pin numbers
2017-08-18 Move slide swith to the correct board
2017-08-18 Add footprint for push switch
2017-08-18 Without messing up
2017-08-18 okgo2mini footprints
2017-08-19 footprints for okgo2mini and usbcontrol
2017-08-19 Minified parts, did some order codes
2017-08-20 Very initial placement ideas
2017-08-20 Replace toggle switch on ignitionmini with slide
2017-08-20 Si5515 fire switch, DPDT switch 5V & batt
2017-08-20 Fix project file
2017-08-21 Tweak usbcontrol into silly dongle board
